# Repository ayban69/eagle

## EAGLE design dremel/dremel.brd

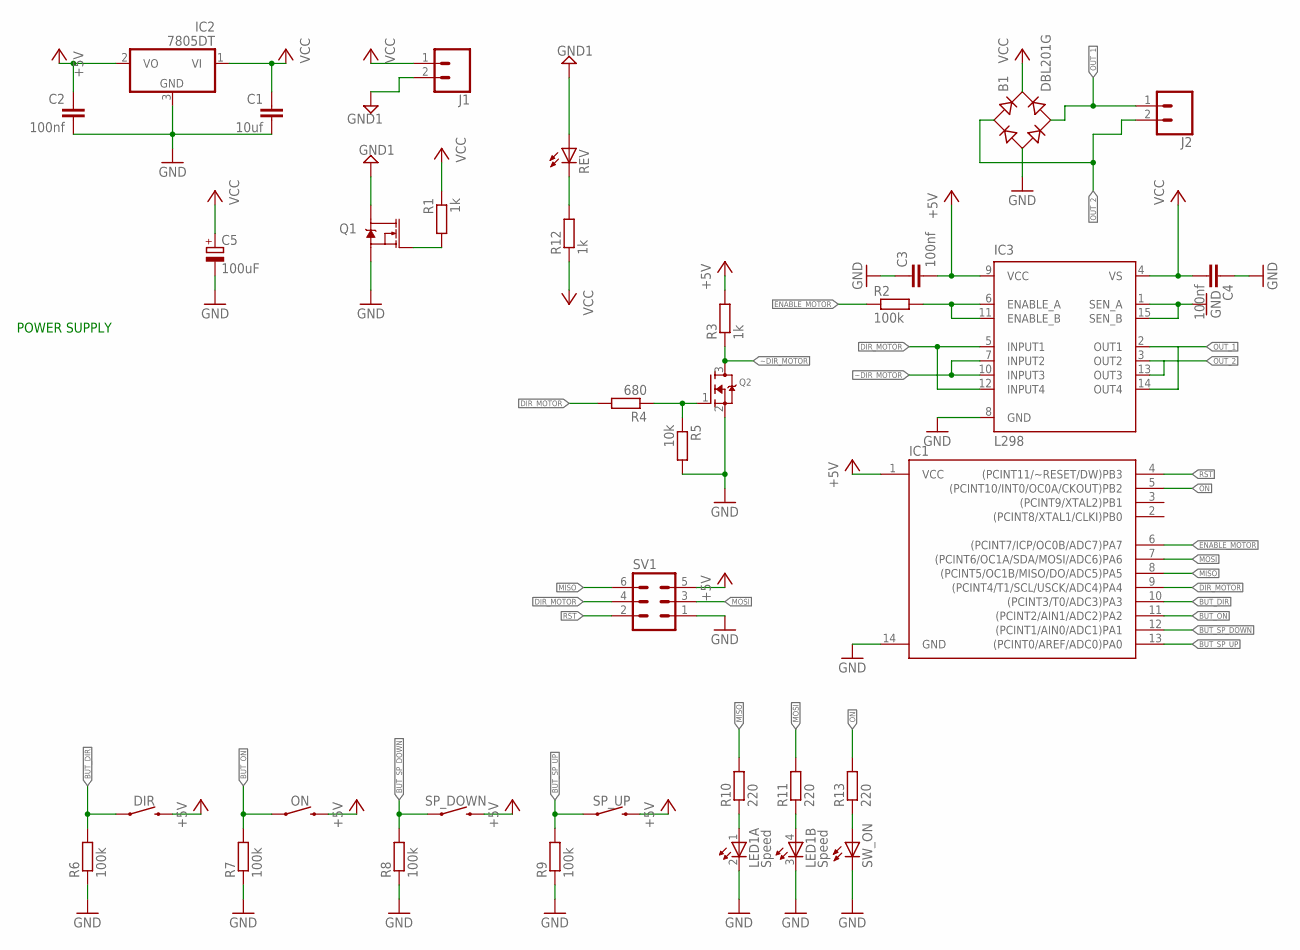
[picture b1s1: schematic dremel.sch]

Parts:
B1: DBL201G; DB
C1: 10uf; C1206
C2, C3, C4: 100nf; C1206
C5: 100uF; E5-10,5
DIR: MOMENTARY-SWITCH-SPST-SMD-5.2MM; TACTILE_SWITCH_SMD_5.2MM
IC1: ATTINY84ATTINY84-20PU; DIP14
IC2: 7805DT; TO252
IC3: L298; MULTIWATT-15
J1, J2: CONN_025MM; SCREWTERMINAL-5MM-2
LED1: Speed; P-LCC-4/2
ON: MOMENTARY-SWITCH-SPST-SMD-5.2MM; TACTILE_SWITCH_SMD_5.2MM
Q1: MOSFET-NCH-FDD8780; DPAK
Q2: MOSFET-NREFLOW; SOT23
R1: 1k; R0805
R2, R6, R7, R8, R9: 100k; M0805
R3, R12: 1k; M0805
R4: 680; M0805
R5: 10k; M0805
R10, R11, R13: 220; M0805
REV: LEDSML0805; SML0805
SP_DOWN: MOMENTARY-SWITCH-SPST-SMD-5.2MM; TACTILE_SWITCH_SMD_5.2MM
SP_UP: MOMENTARY-SWITCH-SPST-SMD-5.2MM; TACTILE_SWITCH_SMD_5.2MM
SV1: MA03-2
SW_ON: LEDSML0805; SML0805

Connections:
+5V: C2.1, C3.2, DIR.3 (2), IC1.1 (VCC), IC2.2 (VO), IC3.9 (VCC), ON.3 (2), R3.2, SP_DOWN.3 (2), SP_UP.3 (2), SV1.5
BUT_DIR: DIR.1, IC1.10 ((PCINT3/T0/ADC3)PA3), R6.2
BUT_ON: IC1.11 ((PCINT2/AIN1/ADC2)PA2), ON.1, R7.2
BUT_SP_DOWN: IC1.12 ((PCINT1/AIN0/ADC1)PA1), R8.2, SP_DOWN.1
BUT_SP_UP: IC1.13 ((PCINT0/AREF/ADC0)PA0), R9.2, SP_UP.1
DIR_MOTOR: IC1.9 ((PCINT4/T1/SCL/USCK/ADC4)PA4), IC3.5 (INPUT1), IC3.12 (INPUT4), R4.2, SV1.4
ENABLE_MOTOR: IC1.6 ((PCINT7/ICP/OC0B/ADC7)PA7), R2.1
GND: B1.-, C1.2, C2.2, C3.1, C4.1, C5.-, IC1.14 (GND), IC2.3 (GND), IC3.1 (SEN_A), IC3.8 (GND), IC3.15 (SEN_B), LED1.2 (C), LED1.3 (C), Q1.3 (S), Q2.2 (S), R5.2, R6.1, R7.1, R8.1, R9.1, SV1.1, SW_ON.C
GND1: J1.2, Q1.4 (D), REV.A
MISO: IC1.8 ((PCINT5/OC1B/MISO/DO/ADC5)PA5), R10.2, SV1.6
MOSI: IC1.7 ((PCINT6/OC1A/SDA/MOSI/ADC6)PA6), R11.2, SV1.3
unnamed: Q1.1 (G), R1.2
unnamed: IC3.6 (ENABLE_A), IC3.11 (ENABLE_B), R2.2
unnamed: Q2.1 (G), R4.1, R5.1
unnamed: LED1.1 (A), R10.1
unnamed: LED1.4 (A), R11.1
unnamed: R12.2, REV.C
unnamed: R13.1, SW_ON.A
ON: IC1.5 ((PCINT10/INT0/OC0A/CKOUT)PB2), R13.2
OUT_1: B1.AC2, IC3.2 (OUT1), IC3.14 (OUT4), J2.1
OUT_2: B1.AC1, IC3.3 (OUT2), IC3.13 (OUT3), J2.2
RST: IC1.4 ((PCINT11/~RESET/DW)PB3), SV1.2
VCC: B1.+, C1.1, C4.2, C5.+, IC2.1 (VI), IC3.4 (VS), J1.1, R1.1, R12.1
~DIR_MOTOR: IC3.7 (INPUT2), IC3.10 (INPUT3), Q2.3 (D), R3.1

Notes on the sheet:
POWER SUPPLY

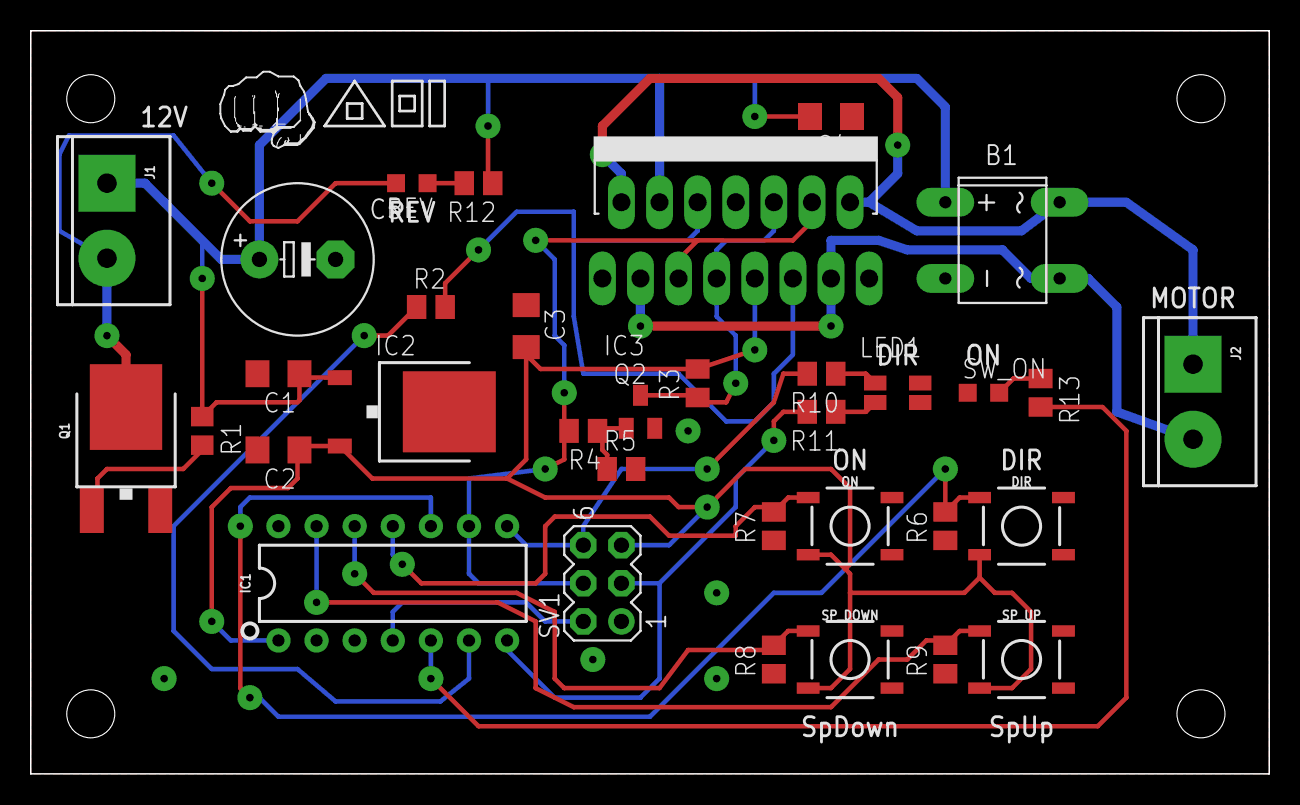
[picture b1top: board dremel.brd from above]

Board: 2 copper layers, 82.5 x 49.5 mm, 35 parts (0 on the bottom side), 24 nets.

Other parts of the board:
U$1: ADILOGO

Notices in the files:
parts and their libraries:
SparkFun-Switches: Licensing: Creative Commons ShareAlike 4.0 International - https://creativecommons.org/licenses/by-sa/4.0
